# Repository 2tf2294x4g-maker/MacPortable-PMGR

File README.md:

# Macintosh Portable PMGR replacement

An open replacement for the **Mitsubishi M50753 power manager (PMGR)** in the Macintosh Portable
and the **PowerBook 100**, which use the same chip. The original chip is irreplaceable when it fails; this is a small two-board stack that solders onto
its footprint and runs open firmware on a Microchip **AVR128DB64**, reproducing the original's
behaviour toward the Mac.

| | |
|---|---|
| **Interposer** | 16.3 mm square, castellated — solders onto the M50753's footprint on the logic board |
| **MCU board** | 20.0 × 23.5 mm — carries the AVR, plugs onto the interposer through a Hirose DF12 connector |
| **J21 breakout** *(optional)* | sits between the two for development, bringing every PMGR signal out to 2.54 mm Dupont headers |

## Photos

<table>
<tr>
<td width="50%"><br><b>Before:</b> the original M50753 (Apple 342S0753-A) at the PMGR position.</td>
<td width="50%"><br><b>After:</b> the replacement stack at the same position.</td>
</tr>
<tr>
<td><br>The interposer soldered to the original footprint. This first batch is labelled <code>PMGR Chip</code>; boards made from the current files say <code>J1</code>.</td>
<td><br>MCU board, top: the AVR128DB64 and the UPDI programming header <code>J2</code>.<br><br><br>Underside: the DF12 socket <code>J1</code>, and the <code>BAT54S</code> + 1 kΩ clamp on the battery-sense line.</td>
</tr>
<tr>
<td><br><b>PowerBook 100:</b> the same stack at U22, beside the VIA. The CPU board fits over it; the wires are the programming header, brought out for development.</td>
<td><br>The PowerBook 100 at the Finder under System 7.5.3, running on the replacement PMGR.<br><br><br>Its PowerBook control panel. The backlight brightness dial works through the replacement.</td>
</tr>
<tr>
<td colspan="2"><br><b>SCSI Disk Mode</b> on the replacement (0.1.16, with the pin-48 wire): HDI-30 pin 1 grounded at startup, and the PowerBook shows its disk-mode screen with SCSI ID 1.</td>
</tr>
</table>

## Status — version 0.1, prototype

**Working in a Macintosh Portable and, since 0.1.15, a PowerBook 100.**

- **Macintosh Portable M5120** (the original, non-backlit model): it boots, sleeps and wakes, shuts down
  and honours the reset switch under System 6.0.8 and 7.5.3, and a supervised fast charge terminates
  correctly. A second, unmodified Portable is kept as the reference. **The backlit Portable (M5126)
  has not been tried.**
- ⭐ **PowerBook 100** (one machine, System 7.5.3): it boots to the Finder, the **brightness dial**
  works, it sleeps and wakes, and Mac OS shows its whole low-battery sequence and then sleeps the
  machine. The same boards and the same firmware fit both machines; no PowerBook-specific build is
  needed. ⭐ Since 0.1.16, **SCSI Disk Mode works** with one extra wire on the boards (below).
  **Not yet:** charging (no battery for it yet, so it is uncalibrated and ran on a bench supply), and
  a closed case. See [`docs/VERIFIED.md`](docs/VERIFIED.md#powerbook-100).

**0.1.16 makes SCSI Disk Mode work on the PowerBook 100**, and fixes two more registers the Mac can read:
- **Disk mode:** the SCSI Disk Adapter grounds a pin on the HDI-30 port, which reaches the PMGR's
  **pin 48**. The boards don't connect pin 48 yet, so it needs **one hand-added wire** through the
  connector's spare position 50 ([`docs/BUILD.md`](docs/BUILD.md)). With it, grounding that pin at
  startup gives the PowerBook's SCSI disk-mode screen, as the original does. Without it, the machine
  simply boots normally, and the same firmware still runs a Portable.
- **The internal disk's power at startup:** the PowerBook 100 ROM checks one PMGR port bit at every
  boot and switched the internal disk's power off when it read 0, as it did on 0.1.15 and earlier.
  It now reads 1, as on the original.
- **The clock through the memory-read command** (`$25`–`$29`) came back byte-reversed, and its
  checksum read 0. Both now match the original. The normal time commands were always correct.

**0.1.15 brought the PowerBook 100 up, and fixed two things every earlier version got wrong:**
- ⛔ **The PWM output (M50753 pin 57) was never driven** on 0.1.14 and earlier, because of an
  AVR128DB silicon erratum. On the Portable that line is the **LCD contrast**, so the contrast control
  could not have worked; it went unnoticed because the development Portable's original LCD is not
  connected. On the PowerBook 100 the line is the **backlight brightness**. Now fixed: measured with
  a scope on the Portable, and seen on the PowerBook's backlight.
- **A register the PowerBook 100 ROM reads** (`$EE`) answered 0, which made the PowerBook boot
  straight into SCSI Disk Mode. It now answers as the original does, and seven more of the
  original's port and PWM registers now read back as they do on the original.
- The battery-reading self-check (`DBG2`) now uses an internal reference, so it gives the same verdict
  on both machines and is valid as soon as power is applied.

Earlier releases: **0.1.12 fixed how fast charge is handled across sleep** (on 0.1.11 and earlier,
don't let the Mac sleep during a fast charge) and added support for **replacement (recreation)
hybrids**, which cut the power at a higher battery voltage; the calibration record says which hybrid
is fitted. ⛔ **Upgrading from 0.1.11 or earlier: rebuild your `calib.args` with `--hybrid` before
flashing** — see [`docs/BUILD.md`](docs/BUILD.md) §7; the flash tool refuses the old record format.
**0.1.14 lowered the recreation-hybrid warning levels** to about 6.10 V warning / 6.02 V sleep.

It is a **prototype**. Some parts of the charging behaviour have not been characterised on
hardware yet. Read [`docs/VERIFIED.md`](docs/VERIFIED.md) for exactly what has and has not been
shown — before relying on it unattended.

## Before you start: this is fine-pitch soldering

Building and fitting this needs **experienced surface-mount work** — it is not a beginner's kit:

- a **0.5 mm-pitch TQFP-64** (the AVR) and two **50-pin, 0.5 mm-pitch** Hirose DF12 connectors;
- **0402** resistors and capacitors (about 1 × 0.5 mm), several on the board's **underside**;
- removing the original **60-lead power manager** from the Mac's logic board (U22 on a PowerBook 100), then soldering the
  interposer's **castellated edges** onto that footprint.

You'll want a hot-air station with preheat, a fine-tip iron, flux, solder wick, and magnification —
a stereo microscope makes this far easier. Having the fab assemble the MCU board removes most of the
0.5 mm work; removing the original chip and fitting the interposer still has to be done by hand.
See [`docs/BUILD.md`](docs/BUILD.md).

## ⛔ Safety — read before you start

- **The battery-sense input of an ORIGINAL M50753 is unprotected.** On a machine still carrying
  the original chip, never put more than **6.5 V** on the battery input while probing; over-driving
  that pin is a documented way to destroy the chip. (This design adds a clamp on that line.)
  The same applies to a **PowerBook 100**: its battery sense is the same circuit.
  The same applies to a **PowerBook 100**, whose battery sense is the same circuit.
- **Never take power from the floppy connector (J15)** for accessories such as an LCD controller.
  It destroyed a PMGR during development.
- **Supervise the first charge.** The charger was designed for the original Gates/EnerSys Cyclon
  cells, which accept an unlimited initial current. Many modern substitute packs are rated far lower.
- **Every flash must re-write the calibration record** (see [`docs/BUILD.md`](docs/BUILD.md)).
  Without it the firmware deliberately refuses to fast-charge.
- **After any programmer operation — flash, fuses, even just reading the device ID — unplug the
  programmer and power-cycle the machine** (supply or battery disconnected) before expecting it to
  start. Otherwise a machine that is shut down may not wake from the keyboard. While the programmer
  is connected it **back-feeds the board**, so switching off is not a power cycle.

## Repository

```
docs/BUILD.md             start here: order, assemble, program, calibrate, install
docs/PROGRAMMING.md       building the firmware and flashing the AVR, step by step
docs/VERIFIED.md          what has been shown on hardware, and what has not
docs/REFERENCE-MEASUREMENTS.md  known-good voltages and pin references to check against
docs/ASSEMBLY.md          the detailed, bench-tested assembly procedure
docs/PINOUT.md            M50753 pin -> interposer -> AVR mapping
docs/MCU-BOARD-SCHEMATIC.md
docs/BOM.md, ORDER-LIST.md
hardware/mcu-board/       MCU board rev A (built and tested): KiCad board + Gerbers
hardware/interposer-v2/   interposer rev A (built and tested): KiCad board + Gerbers
hardware/mcu-revb/        MCU board rev B: disk-mode path, edge pads, fits the Portable's closed case (not yet fabricated)
hardware/interposer-revb/ interposer rev B: disk-mode line built in (not yet fabricated)
hardware/breakout-j21/    bench tool: J21 breakout, built and used on the Portable
hardware/breakout-pb100/  bench tool: PowerBook 100 breakout, should work in both (not yet fabricated)
hardware/carrier-m50753/  bench tool: carrier for an ORIGINAL M50753 on the interposer (not yet fabricated)
firmware/                 AVR firmware, host-side unit tests, fuse policy
tools/                    flashing and calibration scripts
```

## The ROM image

The M50753 carries a small program ROM that the Mac can read back. **The default build contains a
synthetic image — no Apple code anywhere in this repository.** A byte-exact build is possible if you
supply your own dump of the original ROM; see [`firmware/README.md`](firmware/README.md). Never
commit that dump.

## Licences

- Hardware (`hardware/`): **CERN Open Hardware Licence v2 — Strongly Reciprocal** (`LICENSE`)
- Firmware and tools (`firmware/`, `tools/`): **MIT** (`LICENSE-MIT`)

This repository is the clean release. The full development record — every measurement, the
mistakes and their corrections — is kept separately. Questions and results from other machines are
welcome as issues; readings from original, un-modified Portables are especially useful.

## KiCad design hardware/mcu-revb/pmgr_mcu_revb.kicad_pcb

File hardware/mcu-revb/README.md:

# MCU board — rev B

The same circuit as the [rev A MCU board](../mcu-board/README.md) (AVR128DB64, decoupling, the
battery-sense clamp, DF12 socket `J1`, UPDI header `J2`), with three changes: the **SCSI Disk Mode
path**, **edge pads** for programming and debugging inside the machine, and the whole board moved
**5 mm** so the **Portable's case closes** over it.

> ⚠️ **Status: designed and checked, not yet fabricated.** Rev A is the version that has been built
> and tested. Its fit was checked with a 3D-printed model of the outline at the real heights, which
> fits under both machines' cases.

## What rev B fixes

| | rev A | rev B |
|---|---|---|
| **SCSI Disk Mode** (PowerBook 100) | DF12 position 50 not connected: needs the hand-added wire in [`BUILD.md`](../../docs/BUILD.md) | **DF12 position 50 → AVR pin 46 (PF2)**, routed on the board. With the [rev B interposer](../interposer-revb/README.md): disk mode with no wire |
| **Portable, case closed** | **does not fit**: the case catches the board's edge opposite `J2` and tilts it (fine in the PowerBook 100) | **fits**: the board sits **5 mm toward the `J2` end**; the DF12 socket stays where the interposer's header is, so it still mates exactly |
| Programming / debug inside the machine | only through `J2` | bare **edge pads**: `UPDI`, `GND`, `DBG2`, each in line with the `J2` pin of the same signal. No +5 V pad, so a harness cannot back-feed the Mac |
| Labels | partial | every part numbered **with its value** (`C1 100n` …); `J2` pin names; AVR pin numbers 1/17/33/49 |

Firmware: unchanged. 0.1.16 already reads PF2 for disk mode (with a pull-up, so an unconnected
position 50 reads "not disk mode").

## Which MCU board should I use?

| | Portable | PowerBook 100 |
|---|---|---|
| **rev B** MCU board + **rev B** interposer | ✅ | ✅ disk mode, **no wire** |
| rev B MCU board + rev A interposer | ✅ | ✅ runs; no disk mode unless the interposer gets its half of the wire (castellation 48 → position 50) |
| rev A MCU board (+ either interposer) | ⛔ **case does not close** (works on the bench, case open) | ✅ runs; disk mode only with the hand-added wire |

| | |
|---|---|
| Size | 20.0 × 23.5 mm, as rev A (the outline is moved 5 mm relative to the DF12 socket) |
| Fab | 4 layer · 1.6 mm · ENIG · parts on both sides · vias 0.45 / 0.20 mm, tented |
| Fabrication files | `gerbers/`, `pmgr_mcu_revb_gerbers.zip` |
| Design | `pmgr_mcu_revb.kicad_pcb` (KiCad 10) |

The Gerbers are checked against `pmgr_mcu_revb.kicad_pcb` on every layer each time this repository
is generated. Assembly is as rev A ([`ASSEMBLY.md`](../../docs/ASSEMBLY.md), Step 1); the parts list
is the same.

⚠️ For a PowerBook 100, `J2` must not be a vertical header (9–10 mm of clearance). Leave it off and
use the edge pads, or fit it only on the bench.

| front | back (seen from the back) |
|---|---|
|  |  |

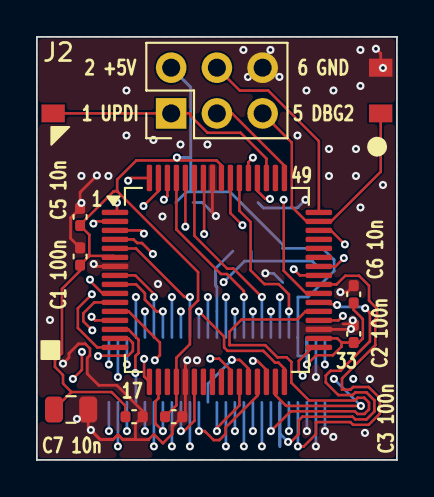
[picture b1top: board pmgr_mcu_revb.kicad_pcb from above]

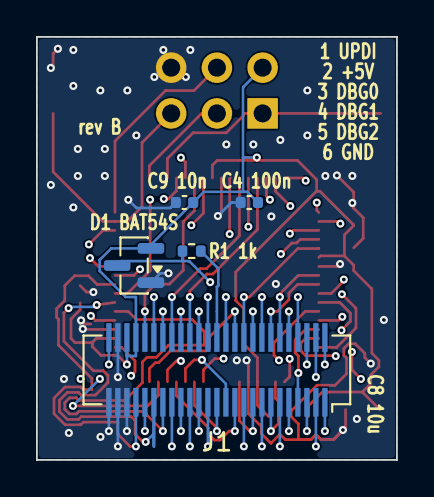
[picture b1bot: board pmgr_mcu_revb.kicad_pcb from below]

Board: 4 copper layers, 20.0 x 23.5 mm, 17 parts (5 on the bottom side), 51 nets.

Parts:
C1, C2, C3, C4: 100nF; C_0402_1005Metric
C5, C6, C7, C9: 10nF; C_0402_1005Metric
C8: 10uF; C_0805_2012Metric
D1: BAT54S; SOT-23
J1: DF12C3.0-50DS; Hirose_DF12_DF12C3.0-50DS-0.5V_2x25_P0.50mm_Vertical
J2: UPDI; PinHeader_2x03_P2.54mm_Vertical
R1: 1k; R_0402_1005Metric
TP1: EDGE_UPDI; EdgePad_1.3x1.0mm
TP2: EDGE_GND; EdgePad_1.3x1.0mm
TP3: EDGE_DBG2; EdgePad_1.3x1.0mm
U1: AVR128DB64; TQFP-64_10x10mm_P0.5mm

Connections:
+5V: C1.1, C2.1, C3.1, C4.1, C5.1, C6.1, C7.1, C8.1, C9.1, D1.2, J1.47, J1.48, J2.2, U1.6, U1.20, U1.34, U1.56
ADC_IN: D1.3, R1.2, U1.26
AD_FILTER: J1.38, R1.1
AKD: J1.18, U1.36
CHRG_ON_N: J1.20, U1.38
DBG0: J2.3, U1.49
DBG1: J2.4, U1.48
DBG2: J2.5, TP3.1, U1.47
DISK_MODE_N: J1.50, U1.46
DISP_BLANK_N: J1.11, U1.29
FDB: J1.12, U1.28
GND: C1.2, C2.2, C3.2, C4.2, C5.2, C6.2, C7.2, C8.2, C9.2, D1.1, J1.23, J1.24, J1.25, J1.49, J2.6, TP2.1, U1.7, U1.21, U1.35, U1.57
HD_PWR_N: J1.43, U1.59
HICHG: J1.22, U1.40
IWM_CNTRL: J1.41, U1.61
KBD_RST_N: J1.21, U1.39
MINUS5_EN: J1.16, U1.53
MODEM_AB: J1.14, U1.42
MODEM_INS_N: J1.10, U1.30
MODEM_PWR_N: J1.44, U1.58
OFF_HOOK: J1.40, U1.17
ONESEC_N: J1.2, U1.15
PMACK_N: J1.32, U1.9
PMGCLK_F: J1.9, U1.22
PMGR_ADB: J1.13, U1.27
PMGR_IN0: J1.37, U1.33
PMGR_PWM: J1.36, U1.32
PMGR_RESET_N: J1.8, U1.13
PMINT_N: J1.1, U1.10
PMREQ_N: J1.31, U1.8
RESET_N: J1.6, U1.12
RING_DETECT: J1.15, U1.41
SCC_CNTRL: J1.42, U1.60
SERIAL_PWR_N: J1.45, U1.55
SIXTYHZ: J1.7, U1.18
SOUND_LATCH: J1.39, U1.16
SOUND_OFF: J1.3, U1.31
SOUND_PWR_N: J1.46, U1.54
STOP_CLK: J1.19, U1.37
SYS_PWR_N: J1.17, U1.52
SYS_RST_N: J1.5, U1.11
UPDI: J2.1, TP1.1, U1.51
VIAD0: J1.30, U1.62
VIAD1: J1.29, U1.63
VIAD2: J1.28, U1.64
VIAD3: J1.27, U1.1
VIAD4: J1.26, U1.2
VIAD5: J1.33, U1.3
VIAD6: J1.34, U1.4
VIAD7: J1.35, U1.5
VIA_TEST: J1.4, U1.14

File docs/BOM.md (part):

# PMGR Recreation — Bill of Materials

Generated from the board files, not from the design docs — `pmgr_mcu.kicad_pcb`, `pmgr_breakout.kicad_pcb`, `pmgr_interposer_v2.kicad_pcb`. Reference designators, packages and side-of-board are what will actually be fabricated.

Quantities are **per board** and **for 3 assemblies** (PowerBook 100 bring-up, Portable, spare).

---

## Board 1 — MCU board (`pmgr_mcu`)

4 layer · 1.6 mm · ENIG · 20.0 × 23.5 mm · two-sided assembly

| Ref | Value | Package | Side | Qty/bd | Qty ×3 | Note |
|---|---|---|---|---|---|---|
| U1 | AVR128DB64-I/PT | TQFP-64 10×10 P0.5 | Top | 1 | **4** | DigiKey 12807611. Order a spare — awkward to rework. |
| J1 | **DF12NC(3.0)-50DS-0.5V(51)** | Hirose DF12N 50-pos | **Bottom** | 1 | **3** | Socket. Mates the interposer header. Original DF12C is obsolete — see Connectors below. |
| J2 | 2×3 header 2.54 mm THT | PinHeader_2x03 | Top | 1 | **3** | UPDI + DBG0/1/2. **Trim pins after soldering.** |
| D1 | BAT54S | SOT-23 | **Bottom** | 1 | **3** | Dual Schottky, ADC clamp. |
| R1 | 1 kΩ | 0402 | **Bottom** | 1 | 3 | |
| C1, C2, C3 | 100 nF X7R | 0402 | Top | 3 | 9 | Decoupling |
| C4 | 100 nF X7R | 0402 | **Bottom** | 1 | 3 | Decoupling |
| C5, C6, C7 | 10 nF X7R | 0402 | Top | 3 | 9 | Decoupling |
| C9 | 10 nF X7R | 0402 | **Bottom** | 1 | 3 | Added after the pin audit found pins 56/57 unconnected |
| C8 | 10 µF X5R | 0805 | Top | 1 | 3 | Bulk |

**14 placements per board, 5 of them on the bottom side** — the board needs a two-sided stencil and two reflow passes, or bottom-side hand work. C4, C9, D1, R1 and the DF12 socket are all underneath.

**Four decoupling pairs, not three.** The AVR128DB64 has two VDD/GND pairs (6/7 and 56/57) plus AVDD and VDDIO2 — four supply pins.

---

## Board 2 — Interposer (`pmgr_interposer_v2`)

4 layer · 1.6 mm · ENIG · 16.3 × 16.3 mm · **castellated plating on all 60 half-holes**

| Ref | Value | Package | Side | Qty/bd | Qty ×3 | Note |
|---|---|---|---|---|---|---|
| J1 | **DF12NC(3.0)-50DP-0.5V(51)** | Hirose DF12N 50-pos | Top | 1 | **3** | Header. Mates the MCU board socket. |
| U1 | — (land pattern only) | PMGR_Castellation_60 | Top | 0 | 0 | Not a part. The 60 castellations that solder to the Portable's PMGR pads. |

> ℹ️ **Reference designator fixed 2026-08-26.** It was `PMGR Chip` (invalid — contains a space) and is now `J1`. The change was made AFTER the boards were ordered, so **boards from this run are silkscreened `PMGR Chip`**; a future run will read `J1`. Nothing electrical differs. The as-fabricated files are frozen in `interposer-v2/as-built-2026-08-26/`.

Only **one part** is placed on the interposer. Everything else about it is copper.

---

## Board 3 — Debug breakout (`pmgr_breakout`) — bench tool, optional

**2 layer** · 1.6 mm · **HASL** · 27 × 40 mm

> ⭐ **Order this one HASL, not ENIG.** The 2026-08-27 order specified ENIG and
> paid **$42.41** instead of **$5.00** — specifying it dropped the board out of
> PCBWay's $5-for-5 promotional tier. Nothing on this board needs ENIG: no
> fine-pitch parts, only through-hole 1.27 mm headers. See `ORDER-LIST.md`.

| Ref | Value | Package | Side | Qty/bd | Qty ×1 | Note |
|---|---|---|---|---|---|---|
| J1 | **DF12NC(3.0)-50DS-0.5V(51)** | Hirose DF12N 50-pos | **Bottom** | 1 | **1** | Socket — receives the interposer |
| J2 | **DF12NC(3.0)-50DP-0.5V(51)** | Hirose DF12N 50-pos | Top | 1 | **1** | Header — receives the MCU board |
| J3 | **FTS-113-01-L-D** | 2×13 1.27 mm **THT** | Top | 1 | **1** | Signals at positions 1–26 |
| J4 | **FTS-113-01-L-D** | 2×13 1.27 mm **THT** | Top | 1 | **1** | Signals at positions 27–50 (24 used, 2 spare) |
| H1 | 2.2 mm mounting hole | — | — | 1 | — | Not a part |

Build **one**. It comes out before the machine is closed.

---

## Consolidated order

### Semiconductors
| Qty | Part | Package |
|---|---|---|
| 4 | AVR128DB64-I/PT | 64-TQFP |
| 3 | BAT54S | SOT-23 |

### Connectors — order the mated pair together
| Qty | Part | Goes on |
|---|---|---|
| **4-5** | Hirose **DF12NC(3.0)-50DP-0.5V(51)** — header | Interposer ×3, breakout ×1 |
| **4-5** | Hirose **DF12NC(3.0)-50DS-0.5V(51)** — socket | MCU board ×3, breakout ×1 |
| 3-5 | **PRPC003DAAN-RC** 2×3, 2.54 mm THT (DK `35-PRPC003DAAN-RC-ND`) | MCU board J2 |
| 2 | **FTS-113-01-L-D** 2×13, 1.27 mm THT (Mouser `200-FTS11301LD`) | Breakout J3, J4 |
| — | 1.27 mm → 0.1″ IDC cables | Logic analyser |

> ⚠️ **Stack height must match on both halves, and must be (3.0).** The land pattern is identical across 3.0/3.5/4.0/5.0, so a wrong-height part solders down perfectly and silently fails to mate. **Mate one socket to one header by hand before reflowing anything** — while they are still two loose parts.

### Passives — buy in 100s, they cost nothing
| Qty | Value | Package |
|---|---|---|
| 12 | 100 nF X7R | 0402 |
| 12 | 10 nF X7R | 0402 |
| 3 | 10 µF X5R | 0805 |
| 3 | 1 kΩ | 0402 |

### Not a part, but required before first fit
**Kapton tape**, cut to the interposer outline — the third mitigation against shorting to the logic board, and the only one not solved in the PCB itself. The Portable's U15H footprint has live traces and vias inside it.

### Programming
One of: USB-serial adapter + 4.7 kΩ (cheapest, `Makefile` flash target already uses `pymcuprog`), MPLAB SNAP, or Atmel-ICE.

> ⚠️ Confirm your programmer's UPDI pin position against J2: **pin 1 = UPDI, pin 2 = +5 V, pin 6 = GND.** Pins 2 and 6 are standard; tools differ on UPDI — some expect pin 5.

---

## ⚠️ Connectors — RESOLVED 2026-08-26, do not re-derive

The original Hirose parts are **obsolete**. Ordering these three, and only these three:

| Role | Part | Distributor | Qty |
|---|---|---|---|
| Socket — MCU ×3, breakout J1 | **DF12NC(3.0)-50DS-0.5V(51)** | Mouser | 4-5 |
| Header — interposer ×3, breakout J2 | **DF12NC(3.0)-50DP-0.5V(51)** | Mouser | 4-5 |
| Breakout J3, J4 | **FTS-113-01-L-D** (Mouser 200-FTS11301LD) | Mouser | 2 |

### Why DF12**NC** and not DF12**NB**

`DF12C(3.0)-50DS-0.5V(81)` and `DF12E(3.0)-50DP-0.5V(81)` both went obsolete. General sources name **DF12NB** as the DF12 successor. **That is wrong for these boards.**

- **NB = *with* metal fitting** — its recommended pattern adds two lands (`0.8`, `1.8`). Our footprint has 50 copper pads and nothing else, so the fitting legs would land on bare soldermask.
- **NC = *without* metal fitting** — matches exactly. The obsolete parts were specified "W/O BOS,**FIT**" (without boss, without fitting), so NC is the true equivalent.

Verified against the DF12N catalog's *Recommended PCB mounting pattern*, "without metal fitting" variant:

| | Board (from `pmgr_mcu.kicad_pcb`) | DF12N w/o fitting |
|---|---|---|
| Pitch | 0.50 mm | 0.5 ±0.02 |
| Pad size | 0.30 × 1.60 mm | 0.3 ±0.02 × 1.6 ±0.02 |
| Row spacing | 3.60 mm | 2 + 1.6 = 3.6 |
| Span | 12.00 mm | B = 12.0 |
| Extra lands | none | none |

Keep **(3.0)** stack height — every clearance figure in `CLEARANCE-MEASUREMENTS.md` assumes it. 4.0 mm would also fit vertically (and improves VIA clearance from 0.5 to 1.5 mm) but invalidates the measured numbers.

### Why FTS-113-01-**L-D**

J3/J4 are **through-hole** (0.65 mm drills; the 113 PTH holes in the drill file are 61 vias + 26 + 26). Two wrong turns worth recording:

- **FTSH series is SMT-only** — its catalog is titled *Surface Mount Micro Header*. `-DV`/`-DH`/`-MT` are tail *orientations*, not mounting types.
- **In FTS, the Row Option decides mounting**: `-D` = Double **Through-hole**, `-DV` = Double Vertical **SMT**. `-P` (Pick & Place Pad) is an SMT-assembly option and indicates a surface-mount part.

Lead style matters too: **-01 = 3.05 mm post, mates FFSD** (the 1.27 mm IDC ribbon socket a logic analyser uses). `-03` = 1.65 mm mates CLP, a board-mounted socket strip — too short to hold a cable.

> Confirm your analyser's cable is an FFSD-style IDC socket. If it uses flying leads with micro-clips, post length is irrelevant and `-03` would do.

---

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
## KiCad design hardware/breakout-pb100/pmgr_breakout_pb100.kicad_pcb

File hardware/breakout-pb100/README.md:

# PowerBook 100 breakout — bench tool

> 🧪 **Bench tool, not part of the replacement.** It sits between the interposer and the MCU board with
> the case open, brings every PMGR signal out for a logic analyser, and comes out before the machine is
> closed. **Designed and checked, not yet fabricated:** it should work in both machines; the
> [J21 breakout](../breakout-j21/README.md) is the one that has been built and used (on the Portable).

The [J21 breakout](../breakout-j21/README.md) stacks the MCU board directly above the interposer, about
12 mm tall, which the PowerBook 100's CPU card (about 10.4 mm above U22) does not allow. This one is a long
**cantilever**: the base end plugs onto the interposer under the CPU card, and the MCU board plugs in
at the far end, out in open bench space.

```
  base end (under the CPU card)                                       tip (open bench space)
  J1 DF12 socket underneath → interposer │ J5/J6 2.54 mm headers, J21 numbering │ MCU board on J2 │ J7
```

| | |
|---|---|
| Size | 27 × 113 mm (the tip is 105 mm past the DF12 centre) |
| Fab | 4 layer · 1.6 mm · ENIG (two 0.5 mm DF12 connectors) · vias 0.6 / 0.3 mm, tented |
| Parts | `J1` DF12 socket (`DS`, **bottom**, mates the interposer) · `J2` DF12 header (`DP`, top, **turned 180°**: the MCU board plugs in turned round, its `J2` end toward the tip) · `J5`/`J6` 1×25 2.54 mm (the Portable's J21 pin numbers, odd / even) · `J7` 1×2 2.54 mm: `DISK_MODE_N` (DF12 position 50, M50753 pin 48) and GND |
| Fabrication files | `gerbers/` (with `pmgr_breakout_pb100_gerbers.zip`) |
| Design | `pmgr_breakout_pb100.kicad_pcb` (KiCad 10) — see `BOM.md` |

Notes:
- With an MCU board on the tip it is a long lever: support it. `H1` (mid-span) takes a foot or standoff.
  The [rev B MCU board](../mcu-revb/README.md) covers the tip holes `H2`/`H3`, so use `H1`.
- Mate each DF12 pair by hand before soldering: every stack height shares the footprint, and these must be 3.0 mm.
- Cosmetic: a few vias sit under labels, so the drill clips some letters.

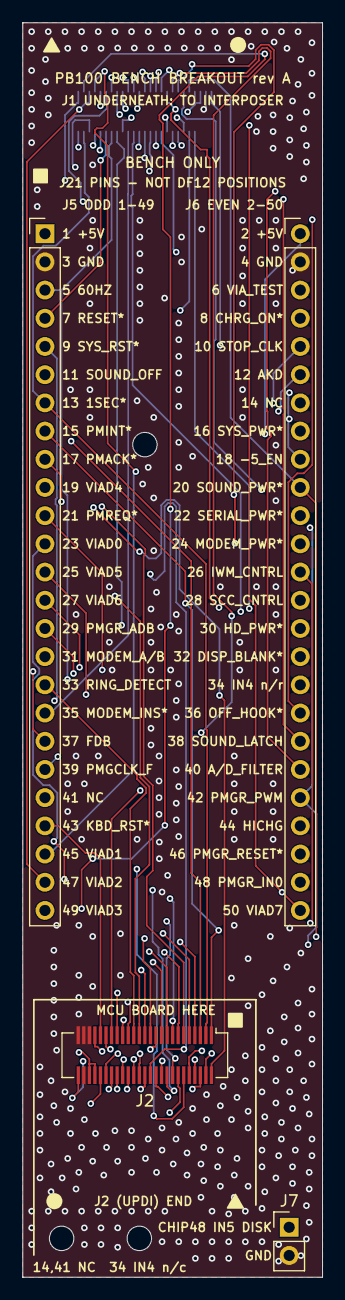
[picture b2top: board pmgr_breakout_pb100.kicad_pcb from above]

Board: 4 copper layers, 27.0 x 113.0 mm, 8 parts (1 on the bottom side), 46 nets.

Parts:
H1, H2, H3: MountingHole; MountingHole_2.2mm
J1: DF12C-50DS (down) to interposer; Hirose_DF12_DF12C3.0-50DS-0.5V_2x25_P0.50mm_Vertical
J2: DF12E-50DP (up) MCU board; Hirose_DF12_DF12E3.0-50DP-0.5V_2x25_P0.50mm_Vertical
J5: J21 ODD 1-49; PinHeader_1x25_P2.54mm_Vertical
J6: J21 EVEN 2-50; PinHeader_1x25_P2.54mm_Vertical
J7: IN5 DISK_MODE / GND; PinHeader_1x02_P2.54mm_Vertical

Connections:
+5V: J1.47, J1.48, J2.47, J2.48, J5.1, J6.1
AD_FILTER: J1.38, J2.38, J6.20
AKD: J1.18, J2.18, J6.6
CHRG_ON_N: J1.20, J2.20, J6.4
DISK_MODE_N: J1.50, J2.50, J7.1
DISP_BLANK_N: J1.11, J2.11, J6.16
FDB: J1.12, J2.12, J5.19
GND: J1.23, J1.24, J1.25, J1.49, J2.23, J2.24, J2.25, J2.49, J5.2, J6.2, J7.2
HD_PWR_N: J1.43, J2.43, J6.15
HICHG: J1.22, J2.22, J6.22
IWM_CNTRL: J1.41, J2.41, J6.13
KBD_RST_N: J1.21, J2.21, J5.22
MINUS5_EN: J1.16, J2.16, J6.9
MODEM_AB: J1.14, J2.14, J5.16
MODEM_INS_N: J1.10, J2.10, J5.18
MODEM_PWR_N: J1.44, J2.44, J6.12
OFF_HOOK: J1.40, J2.40, J6.18
ONESEC_N: J1.2, J2.2, J5.7
PMACK_N: J1.32, J2.32, J5.9
PMGCLK_F: J1.9, J2.9, J5.20
PMGR_ADB: J1.13, J2.13, J5.15
PMGR_IN0: J1.37, J2.37, J6.24
PMGR_PWM: J1.36, J2.36, J6.21
PMGR_RESET_N: J1.8, J2.8, J6.23
PMINT_N: J1.1, J2.1, J5.8
PMREQ_N: J1.31, J2.31, J5.11
RESET_N: J1.6, J2.6, J5.4
RING_DETECT: J1.15, J2.15, J5.17
SCC_CNTRL: J1.42, J2.42, J6.14
SERIAL_PWR_N: J1.45, J2.45, J6.11
SIXTYHZ: J1.7, J2.7, J5.3
SOUND_LATCH: J1.39, J2.39, J6.19
SOUND_OFF: J1.3, J2.3, J5.6
SOUND_PWR_N: J1.46, J2.46, J6.10
STOP_CLK: J1.19, J2.19, J6.5
SYS_PWR_N: J1.17, J2.17, J6.8
SYS_RST_N: J1.5, J2.5, J5.5
VIAD0: J1.30, J2.30, J5.12
VIAD1: J1.29, J2.29, J5.23
VIAD2: J1.28, J2.28, J5.24
VIAD3: J1.27, J2.27, J5.25
VIAD4: J1.26, J2.26, J5.10
VIAD5: J1.33, J2.33, J5.13
VIAD6: J1.34, J2.34, J5.14
VIAD7: J1.35, J2.35, J6.25
VIA_TEST: J1.4, J2.4, J6.3

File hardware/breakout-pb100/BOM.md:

# breakout-pb100 — BOM

Build **one**. A bench jig for the PowerBook 100 with the case open; it comes out before the machine is closed.

| Ref | Value | Package | Side | Qty | Note |
|---|---|---|---|---|---|
| J1 | **DF12NC(3.0)-50DS-0.5V(51)** | Hirose DF12N 50-pos, 0.5 mm | **Bottom** | 1 | Socket: receives the interposer |
| J2 | **DF12NC(3.0)-50DP-0.5V(51)** | Hirose DF12N 50-pos, 0.5 mm | Top | 1 | Header: receives the MCU board, **turned 180°** (its J2/UPDI end toward the tip) |
| J5 | 1×25 **2.54 mm** pin header | THT | Top | 1 | J21 **ODD** 1–49 |
| J6 | 1×25 **2.54 mm** pin header | THT | Top | 1 | J21 **EVEN** 2–50 |
| J7 | 1×2 **2.54 mm** pin header | THT | Top | 1 | `DISK_MODE_N` (chip pin 48 / IN5, DF12-50) and GND |
| H1–H3 | 2.2 mm holes | — | — | — | Not parts: foot / standoff for the cantilever |

⚠️ Same part-number note as `../breakout-j21/BOM.md`: the footprints say `DF12C` / `DF12E`, the parts to buy are **DF12N**
(DF12C is obsolete). ⛔ Confirm the `(51)` suffix on BOTH halves and that the pair mates before ordering.

## Board spec

```
  4 layer · 1.6 mm · 27 × 113 mm · min track/space 0.15 / 0.15 mm · via 0.6 / 0.3 mm
  stack: F.Cu / In1.Cu (solid GND) / In2.Cu (signals) / B.Cu
```

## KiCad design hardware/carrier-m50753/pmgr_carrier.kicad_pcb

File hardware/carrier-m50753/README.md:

# Original-chip carrier — bench tool

> 🧪 **Bench tool, not part of the replacement.** **Designed and checked, not yet fabricated;** it should
> work in both machines.

Holds an **original M50753** power manager on a small board that plugs onto the interposer's DF12 header
**in place of the MCU board**. An original chip can then move between machines without reflow, and be
compared with the replacement on the same machine. It needs an interposer (rev B for PowerBook 100 SCSI
Disk Mode, as with the MCU board).

| | |
|---|---|
| Size | 27.75 × 21 mm: the chip, plus a tab on one side for the crystal and test pads. Shaped and positioned to fit under the Portable's case and beside the PowerBook 100's CPU card (checked with a 3D-printed model at the real heights) |
| Fab | 4 layer · 1.6 mm · ENIG · parts on both sides · vias 0.45 / 0.20 mm, tented |
| Fabrication files | `gerbers/`, `pmgr_carrier_gerbers.zip` |
| Design | `pmgr_carrier.kicad_pcb` (KiCad 10) — see `BOM.md` |

## What the carrier adds around the chip

| chip pin(s) | on the carrier | why |
|---|---|---|
| 19 Xin / 20 Xout | **its own 3.93216 MHz crystal** + two 33 pF C0G load caps | the clock pins are not carried through the interposer. Crystal: HC-49/US **short** can (3.5 mm), e.g. JYJE S1C39321XWJAC; the tall HC-49/U can does not fit |
| 52 IN1 / 54 IN0 | 1 kΩ + BAT54S clamps to the rails | the analogue inputs of an original chip are unprotected |
| 49 IN4 | 100 kΩ to ground | not carried by the interposer |
| 16 INT2 | tied to RESET* (pin 13), as on the logic boards | |
| 23 VSS | ground | |
| 21 φ | test pad **PHI** | should read **983.04 kHz** (the crystal ÷ 4) once the chip runs |
| 14, 22, 24, 36, 46, 47 | open, as on the logic boards | ⛔ pin 36 (P10) is read by the PowerBook 100's ROM: never tie it |

Test pads on the tab: GND, +5V, PHI, IN0, IN1. Every other PMGR signal is on the breakouts' headers.

⛔ **An original M50753's battery-sense input is unprotected: never put more than 6.5 V on the battery
input** while it is fitted (see the main README's safety section).

Assembly by hand: the bottom side first (DF12 socket, clamps, resistors, C3, C10/C11), then C1/C2 and the
chip on top (drag-solder the 0.8 mm leads), then the crystal last, its leads trimmed flush underneath.

| front | back (seen from the back) |
|---|---|
|  |  |

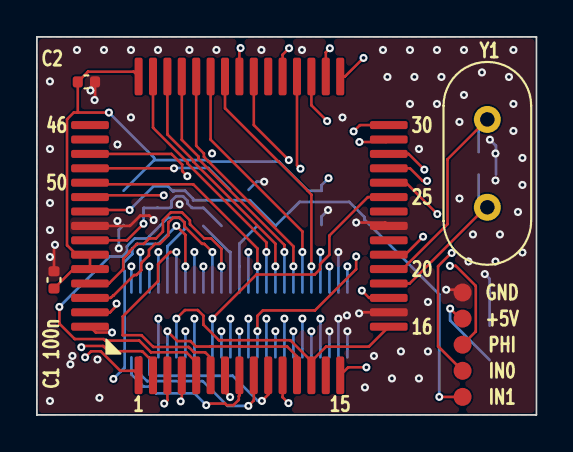
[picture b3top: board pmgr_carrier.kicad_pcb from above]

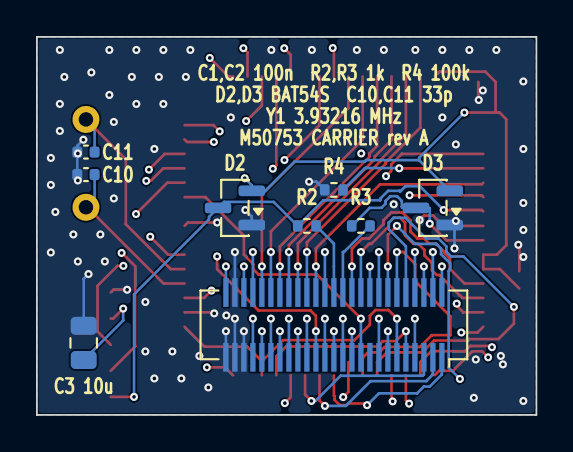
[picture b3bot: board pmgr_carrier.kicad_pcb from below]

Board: 4 copper layers, 27.8 x 21.0 mm, 18 parts (9 on the bottom side), 51 nets.

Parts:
C1, C2: 100nF; C_0402_1005Metric
C3: 10uF; C_0805_2012Metric
C10, C11: 33pF; C_0402_1005Metric
D2, D3: BAT54S; SOT-23
J1: DF12C3.0-50DS; Hirose_DF12_DF12C3.0-50DS-0.5V_2x25_P0.50mm_Vertical
R2, R3: 1k; R_0402_1005Metric
R4: 100k; R_0402_1005Metric
TP1: GND; TestPoint_Pad_D1.0mm
TP2: +5V; TestPoint_Pad_D1.0mm
TP3: PHI; TestPoint_Pad_D1.0mm
TP4: IN0; TestPoint_Pad_D1.0mm
TP5: IN1; TestPoint_Pad_D1.0mm
U1: M50753 (original PMGR); M50753_60P6_QFP60_P0.8mm
Y1: 3.93216MHz JYJE S1C39321XWJAC; Crystal_HC49-4H_Vertical

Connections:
+5V: C1.1, C2.1, C3.1, D2.2, D3.2, J1.47, J1.48, TP2.1, U1.45, U1.55, U1.56
AD_FILTER: J1.38, R2.1
AKD: J1.18, U1.35
CHRG_ON_N: J1.20, U1.33
DISK_MODE_N: J1.50, U1.48
DISP_BLANK_N: J1.11, U1.26
FDB: J1.12, U1.27
GND: C1.2, C2.2, C3.2, C10.2, C11.2, D2.1, D3.1, J1.23, J1.24, J1.25, J1.49, R4.2, TP1.1, U1.17, U1.23, U1.53
HD_PWR_N: J1.43, U1.42
HICHG: J1.22, U1.31
IN0_CHIP: D3.3, R3.2, TP4.1, U1.54
IN1_CHIP: D2.3, R2.2, TP5.1, U1.52
IN4_PD: R4.1, U1.49
IWM_CNTRL: J1.41, U1.44
KBD_RST_N: J1.21, U1.32
MINUS5_EN: J1.16, U1.38
MODEM_AB: J1.14, U1.29
MODEM_INS_N: J1.10, U1.25
MODEM_PWR_N: J1.44, U1.41
OFF_HOOK: J1.40, U1.50
ONESEC_N: J1.2, U1.9
PHI: TP3.1, U1.21
PMACK_N: J1.32, U1.7
PMGR_ADB: J1.13, U1.28
PMGR_IN0: J1.37, R3.1
PMGR_PWM: J1.36, U1.57
PMGR_RESET_N: J1.8, U1.18
PMINT_N: J1.1, U1.8
PMREQ_N: J1.31, U1.6
RESET_N: J1.6, U1.13, U1.16
RING_DETECT: J1.15, U1.30
SCC_CNTRL: J1.42, U1.43
SERIAL_PWR_N: J1.45, U1.40
SIXTYHZ: J1.7, U1.15
SOUND_LATCH: J1.39, U1.51
SOUND_OFF: J1.3, U1.10
SOUND_PWR_N: J1.46, U1.39
STOP_CLK: J1.19, U1.34
SYS_PWR_N: J1.17, U1.37
SYS_RST_N: J1.5, U1.12
VIAD0: J1.30, U1.5
VIAD1: J1.29, U1.4
VIAD2: J1.28, U1.3
VIAD3: J1.27, U1.2
VIAD4: J1.26, U1.1
VIAD5: J1.33, U1.60
VIAD6: J1.34, U1.59
VIAD7: J1.35, U1.58
VIA_TEST: J1.4, U1.11
XIN: C10.1, U1.19, Y1.2
XOUT: C11.1, U1.20, Y1.1

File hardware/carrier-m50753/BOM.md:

# carrier-m50753 — BOM

| Ref | Value | Package | Side | Qty | Part / note |
|---|---|---|---|---|---|
| U1 | **M50753** (original PMGR) | 60P6 QFP, 0.8 mm | Top | 1 | the chip being carried. ⛔ **Soldered, no socket** (PB100 height). Pin 1 at the triangle. |
| J1 | **DF12NC(3.0)-50DS-0.5V(51)** | Hirose DF12N 50-pos socket | **Bottom** | 1 | same as the MCU board's J1. The footprint says DF12C; buy **DF12N** (DF12C is obsolete). ⛔ Check the `(51)` suffix and that it mates with the interposer's header. |
| Y1 | **3.93216 MHz**, 20 pF | HC-49/US short can, 3.5 mm, THT | Top | 1 | **JYJE S1C39321XWJAC**, LCSC **C2764489**, on the circle-side tab. Stand it upright and trim the leads flush underneath. |
| C10, C11 | **33 pF**, C0G | 0402 | Bottom | 2 | crystal load caps (sized for the 20 pF crystal), between Y1's legs |
| C1, C2 | 100 nF, X7R | 0402 | **Top** | 2 | C1 at pins 55/56 (V_REF/AVCC), C2 at pin 45 (VCC), beside their pins |
| C3 | 10 µF, ≥ 10 V | 0805 | Bottom | 1 | bulk, on the back of the tab |
| R2, R3 | 1 kΩ | 0402 | Bottom | 2 | series, IN1 (AD_FILTER) and IN0 |
| R4 | 100 kΩ | 0402 | Bottom | 1 | IN4 pull-down |
| D2, D3 | **BAT54S** | SOT-23 | Bottom | 2 | rail clamps on IN1 / IN0. Same part and orientation as the MCU board's D1. |
| TP1-TP5 | — | 1.0 mm pads | Top | — | not parts: GND, +5V, PHI, IN0, IN1 |

## Board spec

```
  4 layer · 1.6 mm · 27.75 x 21 mm · ENIG (fine-pitch DF12 + QFP) · min track/space 0.15/0.15 · via 0.45/0.20, tented
  two-sided stencil (parts on both faces)
```

Assembly order:
1. Back parts and J1 first, with a stencil or by hand.
2. Then U1 on the top: drag-solder the QFP.
3. Then Y1, through-hole, last.

⚠️ The tab's back faces the logic board 4.6 mm below, so trim Y1's leads.

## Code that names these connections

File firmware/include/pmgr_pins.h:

/* GENERATED by gen_pins.py FROM THE BOARD (mcu-board/pmgr_mcu.kicad_pcb).
 * Do not edit by hand, and do not regenerate from MCU-BOARD-SCHEMATIC.md -
 * the board is what gets fabricated. */
#ifndef PMGR_PINS_H
#define PMGR_PINS_H

#include <avr/io.h>

/* Data bus: all eight bits on PORTA, so a bus read is one instruction.
   The PMGR handshake timing depends on that - never split across ports. */
#define BUS_PORT      PORTA

/*
 * ADB:
 * P4.0 / PD1 PMGR_ADB = control output to an external inverting
 *                       open-collector ADB driver. ⛔ Driven OPEN-DRAIN
 *                       in software - Hi-Z asserts, LOW releases, NEVER
 *                       driven HIGH. See pmgr_adb.c and MEASUREMENTS 2.58.
 * P4.1 / PD2 FDB      = direct ADB bus sense input.
 */

/* ---- PORTA ---- */
#define VIAD0_PORT             PORTA
#define VIAD0_bm               (1U << 0)   /* PA0, TQFP 62 */
#define VIAD1_PORT             PORTA
#define VIAD1_bm               (1U << 1)   /* PA1, TQFP 63 */
#define VIAD2_PORT             PORTA
#define VIAD2_bm               (1U << 2)   /* PA2, TQFP 64 */
#define VIAD3_PORT             PORTA
#define VIAD3_bm               (1U << 3)   /* PA3, TQFP 1 */
#define VIAD4_PORT             PORTA
#define VIAD4_bm               (1U << 4)   /* PA4, TQFP 2 */
#define VIAD5_PORT             PORTA
#define VIAD5_bm               (1U << 5)   /* PA5, TQFP 3 */
#define VIAD6_PORT             PORTA
#define VIAD6_bm               (1U << 6)   /* PA6, TQFP 4 */
#define VIAD7_PORT             PORTA
#define VIAD7_bm               (1U << 7)   /* PA7, TQFP 5 */

/* ---- PORTB ---- */
#define PMREQ_N_PORT           PORTB
#define PMREQ_N_bm             (1U << 0)   /* PB0, TQFP 8 */
#define PMACK_N_PORT           PORTB
#define PMACK_N_bm             (1U << 1)   /* PB1, TQFP 9 */
#define PMINT_N_PORT           PORTB
#define PMINT_N_bm             (1U << 2)   /* PB2, TQFP 10 */
#define SYS_RST_N_PORT         PORTB
#define SYS_RST_N_bm           (1U << 3)   /* PB3, TQFP 11 */
#define RESET_N_PORT           PORTB
#define RESET_N_bm             (1U << 4)   /* PB4, TQFP 12 */
#define PMGR_RESET_N_PORT      PORTB
#define PMGR_RESET_N_bm        (1U << 5)   /* PB5, TQFP 13 */
#define VIA_TEST_PORT          PORTB
#define VIA_TEST_bm            (1U << 6)   /* PB6, TQFP 14 */
#define ONESEC_N_PORT          PORTB
#define ONESEC_N_bm            (1U << 7)   /* PB7, TQFP 15 */

/* ---- PORTC ---- */
#define SOUND_LATCH_PORT       PORTC
#define SOUND_LATCH_bm         (1U << 0)   /* PC0, TQFP 16 */
#define OFF_HOOK_PORT          PORTC
#define OFF_HOOK_bm            (1U << 1)   /* PC1, TQFP 17 */
#define SIXTYHZ_PORT           PORTC
#define SIXTYHZ_bm             (1U << 2)   /* PC2, TQFP 18 */
#define PMGCLK_F_PORT          PORTC
#define PMGCLK_F_bm            (1U << 4)   /* PC4, TQFP 22 */

/* ---- PORTD ---- */
#define ADC_IN_PORT            PORTD
#define ADC_IN_bm              (1U << 0)   /* PD0, TQFP 26 */
#define PMGR_ADB_PORT          PORTD
#define PMGR_ADB_bm            (1U << 1)   /* PD1, TQFP 27 */
#define FDB_PORT               PORTD
#define FDB_bm                 (1U << 2)   /* PD2, TQFP 28 */
#define DISP_BLANK_N_PORT      PORTD
#define DISP_BLANK_N_bm        (1U << 3)   /* PD3, TQFP 29 */
#define MODEM_INS_N_PORT       PORTD
#define MODEM_INS_N_bm         (1U << 4)   /* PD4, TQFP 30 */
#define SOUND_OFF_PORT         PORTD
#define SOUND_OFF_bm           (1U << 5)   /* PD5, TQFP 31 */
#define PMGR_PWM_PORT          PORTD
#define PMGR_PWM_bm            (1U << 6)   /* PD6, TQFP 32 */
#define PMGR_IN0_PORT          PORTD
#define PMGR_IN0_bm            (1U << 7)   /* PD7, TQFP 33 */

/* ---- PORTE ---- */
#define AKD_PORT               PORTE
#define AKD_bm                 (1U << 0)   /* PE0, TQFP 36 */
#define STOP_CLK_PORT          PORTE
#define STOP_CLK_bm            (1U << 1)   /* PE1, TQFP 37 */
#define CHRG_ON_N_PORT         PORTE
#define CHRG_ON_N_bm           (1U << 2)   /* PE2, TQFP 38 */
#define KBD_RST_N_PORT         PORTE
#define KBD_RST_N_bm           (1U << 3)   /* PE3, TQFP 39 */
#define HICHG_PORT             PORTE
#define HICHG_bm               (1U << 4)   /* PE4, TQFP 40 */
#define RING_DETECT_PORT       PORTE
#define RING_DETECT_bm         (1U << 5)   /* PE5, TQFP 41 */
#define MODEM_AB_PORT          PORTE
#define MODEM_AB_bm            (1U << 6)   /* PE6, TQFP 42 */

/* ---- PORTF ---- */
#define DBG2_PORT              PORTF
#define DBG2_bm                (1U << 3)   /* PF3, TQFP 47 */
#define DBG1_PORT              PORTF
#define DBG1_bm                (1U << 4)   /* PF4, TQFP 48 */
#define DBG0_PORT              PORTF
#define DBG0_bm                (1U << 5)   /* PF5, TQFP 49 */

/* ---- PORTG ---- */
#define SYS_PWR_N_PORT         PORTG
#define SYS_PWR_N_bm           (1U << 0)   /* PG0, TQFP 52 */
#define MINUS5_EN_PORT         PORTG
#define MINUS5_EN_bm           (1U << 1)   /* PG1, TQFP 53 */
#define SOUND_PWR_N_PORT       PORTG
#define SOUND_PWR_N_bm         (1U << 2)   /* PG2, TQFP 54 */
#define SERIAL_PWR_N_PORT      PORTG
#define SERIAL_PWR_N_bm        (1U << 3)   /* PG3, TQFP 55 */
#define MODEM_PWR_N_PORT       PORTG
#define MODEM_PWR_N_bm         (1U << 4)   /* PG4, TQFP 58 */
#define HD_PWR_N_PORT          PORTG
#define HD_PWR_N_bm            (1U << 5)   /* PG5, TQFP 59 */
#define SCC_CNTRL_PORT         PORTG
#define SCC_CNTRL_bm           (1U << 6)   /* PG6, TQFP 60 */
#define IWM_CNTRL_PORT         PORTG
#define IWM_CNTRL_bm           (1U << 7)   /* PG7, TQFP 61 */

/* ---- M50753 port -> our port transforms (checked by gen_pins.py) ----
 *
 * Apple operates on whole port BYTES in places (Power_Command; eor Port_P1
 * in BatteryManage; the sleep path). Our bit orders differ per port as a
 * consequence of the interposer routing remap. Any handler consuming a port
 * bitmap MUST apply the right transform - none of them is the identity.
 */
#define PMGR_P0_PORT        PORTG
#define PMGR_P0_EXACT_REVERSAL 1   /* our bit = 7 - P0 bit */

#define PMGR_P1_PORT        PORTE
#define PMGR_P1_SHIFT       (-1)   /* our bit = P1 bit -1 */

/* P3: SPLIT across ports ['B', 'D'] - NO byte-level transform.
 * Byte-wise code for P3 must be written bit-by-bit. */
#define PMGR_P3_SPLIT       1

#define PMGR_P4_PORT        PORTD
#define PMGR_P4_SHIFT       (+1)   /* our bit = P4 bit +1 */

/* Handshake lines are ACTIVE LOW. */
#define ASSERT_LOW(p,m)    ((p).OUTCLR = (m))
#define DEASSERT_HIGH(p,m) ((p).OUTSET = (m))
#define PIN_IS_LOW(p,m)    (((p).IN & (m)) == 0)

#endif /* PMGR_PINS_H */
